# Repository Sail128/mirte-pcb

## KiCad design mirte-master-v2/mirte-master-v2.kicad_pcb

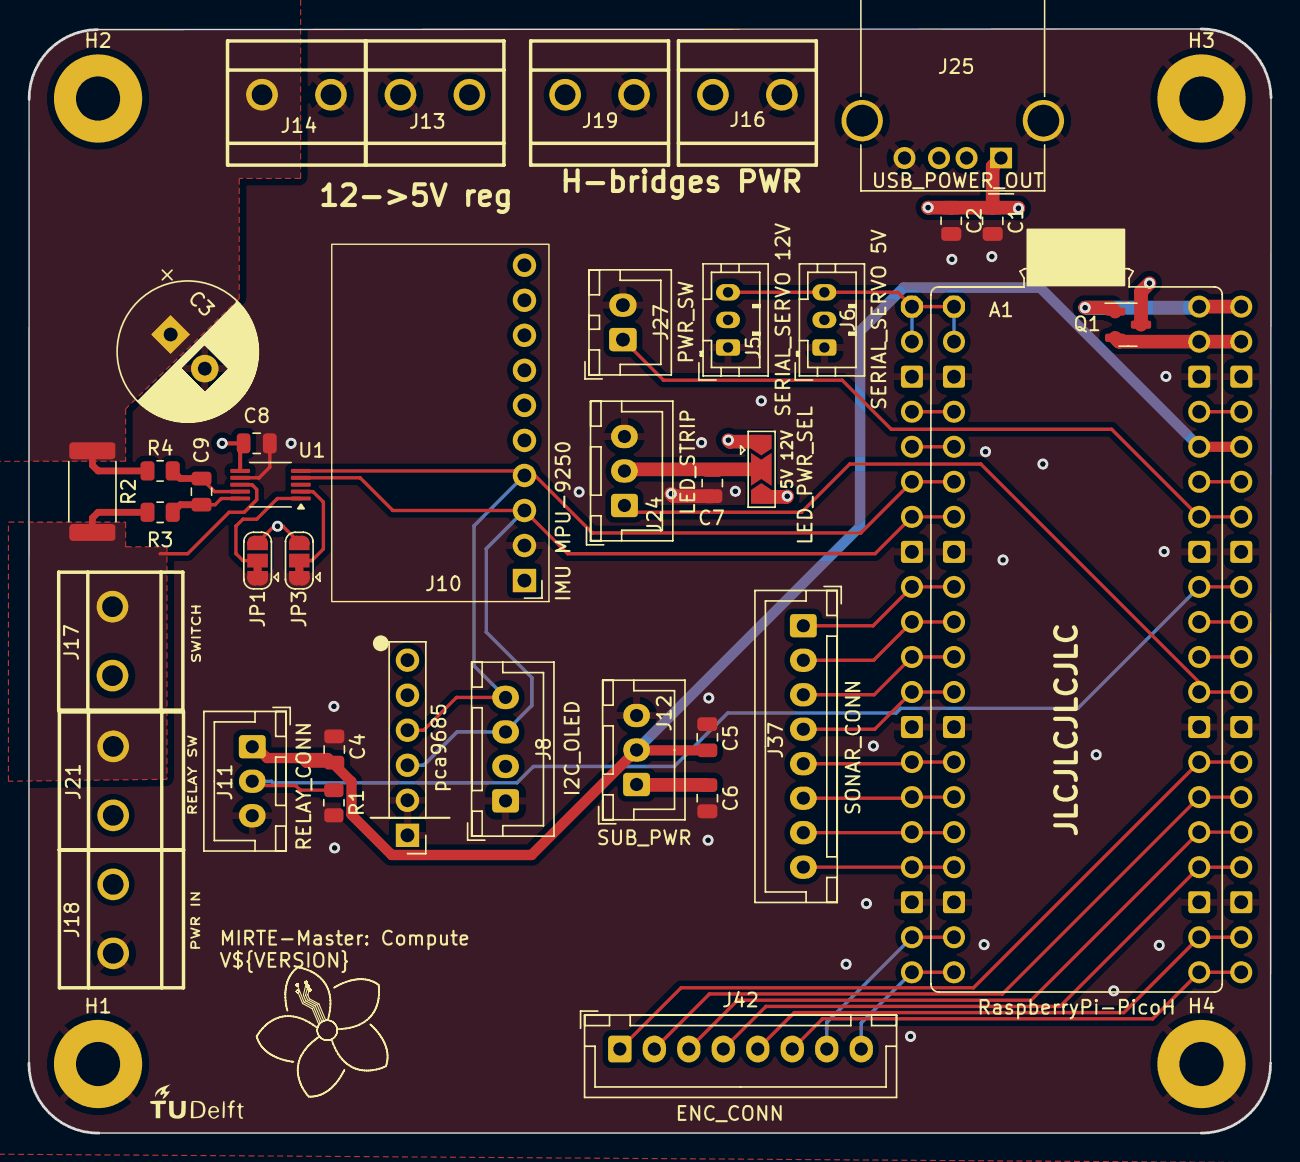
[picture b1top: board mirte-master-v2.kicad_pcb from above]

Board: 4 copper layers, 90.1 x 80.1 mm, 43 parts (0 on the bottom side), 35 nets.

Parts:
A1: RaspberryPi-PicoH; Raspberry_Pi_Pico_double
C1, C4, C5, C6, C8, C9: 100nF; C_0805_2012Metric
C2: 10uF; C_0805_2012Metric
C3: 1000uF; CP_Radial_D10.0mm_P3.50mm
C7: 100uF; C_0805_2012Metric
G1: LOGO; tudelft_logo_10mm
H1, H2, H3, H4: MountingHole_Pad; MountingHole_3.2mm_M3_Pad
J5: servo_connector; JST_PH_B3B-PH-K_1x03_P2.00mm_Vertical
J6: servo_connector_small; JST_PH_B3B-PH-K_1x03_P2.00mm_Vertical
J8: oled_conn; JST_XH_B4B-XH-A_1x04_P2.50mm_Vertical
J9: pca9685; PinHeader_1x06_P2.54mm_Vertical
J10: IMU MPU-9250; MPU9250
J11, J12: Conn_01x03_Pin; JST_XH_B3B-XH-A_1x03_P2.50mm_Vertical
J13, J14, J16, J17, J18, J19, J21: sc; CONN-TH_XY126V-5.0-2P
J24: led_strip; JST_XH_B3B-XH-A_1x03_P2.50mm_Vertical
J25: USB_A; USB_A_Molex_67643_Horizontal
J27: PWR_ON_SWITCH; JST_XH_B2B-XH-A_1x02_P2.50mm_Vertical
J37, J42: Conn_01x08_Pin; JST_XH_B8B-XH-A_1x08_P2.50mm_Vertical
JP1, JP3: SolderJumper_3_Bridged12; SolderJumper-3_P1.3mm_Bridged12_RoundedPad1.0x1.5mm
JP2: LED_POWER_SELECT; SolderJumper-3_P2.0mm_Open_TrianglePad1.0x1.5mm
Q1: DMG2305UX; SOT-23
R1: 680; R_0805_2012Metric
R2: 2mR; R_2512_6332Metric
R3, R4: 4R7; R_0805_2012Metric
U1: INA226; VSSOP-10_3x3mm_P0.5mm

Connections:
+3V3: A1.36 (3V3), C4.1, C5.1, J11.1, J12.2
+5V: C1.1, C2.1, C6.1, C8.1, J6.2, J8.2, J9.5, J9.6, J10.1, J12.1, J13.2, J25.1 (VBUS), JP1.3 (B), JP2.3 (B), JP3.3 (B), Q1.3 (D), U1.6 (VS)
+12V: C3.1, J5.2, J14.1, J16.1, J19.1, JP2.1 (A), R2.1, R4.1
+BATT: J17.1, J18.2, J21.1
/1A: A1.19 (GPIO14), J42.7
/1B: A1.20 (GPIO15), J42.8
/2A: A1.21 (GPIO16), J42.6
/2B: A1.22 (GPIO17), J42.5
/3A: A1.25 (GPIO19), J42.3
/3B: A1.24 (GPIO18), J42.4
/4A: A1.26 (GPIO20), J42.2
/4B: A1.27 (GPIO21), J42.1
/ECHO1: A1.10 (GPIO7), J37.2
/ECHO2: A1.12 (GPIO9), J37.4
/ECHO3: A1.15 (GPIO11), J37.6
/ECHO4: A1.17 (GPIO13), J37.8
/LED_STRIP: A1.29 (GPIO22), J24.1
/POWER_RELAY: A1.32 (GPIO27_ADC1), J11.2, R1.1
/PWR_IN_SIG: A1.34 (GPIO28_ADC2), J27.1
/RX: A1.1 (GPIO0), A1.2 (GPIO1), J5.3, J6.3
/SCL: A1.7 (GPIO5), J8.3, J9.3, J10.3, U1.4 (SDA)
/SDA: A1.6 (GPIO4), J8.4, J9.4, J10.4, U1.5 (SCL)
/TRIGG1: A1.9 (GPIO6), J37.1
/TRIGG2: A1.11 (GPIO8), J37.3
/TRIGG3: A1.14 (GPIO10), J37.5
/TRIGG4: A1.16 (GPIO12), J37.7
/led_strip/LED_PWR: C7.1, J24.2, JP2.2 (C)
/power_input/SWITCHED_PWR: J17.2, J21.2, R2.2, R3.1, U1.8 (Vbus)
GND: A1.3 (GND), A1.8 (GND), A1.13 (GND), A1.18 (GND), A1.23 (GND), A1.28 (GND), A1.33 (AGND), A1.38 (GND), C1.2, C2.2, C3.2, C4.2, C5.2, C6.2, C7.2, C8.2, H1.1, H2.1, H3.1, H4.1, J5.1, J6.1, J8.1, J9.1, J9.2, J10.2, J11.3, J12.3, J13.1, J14.2, J16.2, J18.1, J19.2, J24.3, J25.4 (GND), J25.5 (Shield), J27.2, JP1.1 (A), JP3.1 (A), R1.2, U1.7 (GND)
unnamed: JP1.2 (C), U1.1 (A1)
unnamed: JP3.2 (C), U1.2 (A0)
unnamed: C9.1, R3.2, U1.10 (Vin+)
unnamed: C9.2, R4.2, U1.9 (Vin-)
VBUS: A1.40 (VBUS), Q1.1 (G)
VSYS: A1.39 (VSYS), Q1.2 (S)

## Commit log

2024-10-29 integrated the ina226 in the schematic
2024-10-31 integrated the ina226 in the pcb layout
